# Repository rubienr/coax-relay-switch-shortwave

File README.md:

Shortwave Coax Switch for Antennas
__________________________________
* Very simple schema that switches up to four antenna relays.
* Needs poer just for switching process, remains without during radio operation.
* Up to 1.5KW with GUNNER 18V bistabile 25A AC relay.

Example
_______
The system contains of 4 PCBs:

* The input switch box:
  * 1x switch-matrix (ensures only one relay being active)
  * 1x relais-with-led-indicator (keeps the state, has LED indicator)

* The antenna switch box:
  * 1x switch-matrix (ensures only one relay being active)
  * 1x relais-with-led-indicator (keeps the state, LEDs optional)

Schema and PCB
______________
* Schemas
  * [switch-matrix](https://github.com/rubienr/coax-relay-switch-shortwave/blob/master/docs/switch-matrix-schema.pdf)
  * [relais-with-led-indicator](https://github.com/rubienr/coax-relay-switch-shortwave/blob/master/docs/led-indicator-schema.pdf)
* PCBs
  * [switch-matrix](https://github.com/rubienr/coax-relay-switch-shortwave/blob/master/docs/switch-matrix-pcb.pdf)
  * [relais-with-led-indicator](https://github.com/rubienr/coax-relay-switch-shortwave/blob/master/docs/relais-pcb.pdf)

Pictures
________

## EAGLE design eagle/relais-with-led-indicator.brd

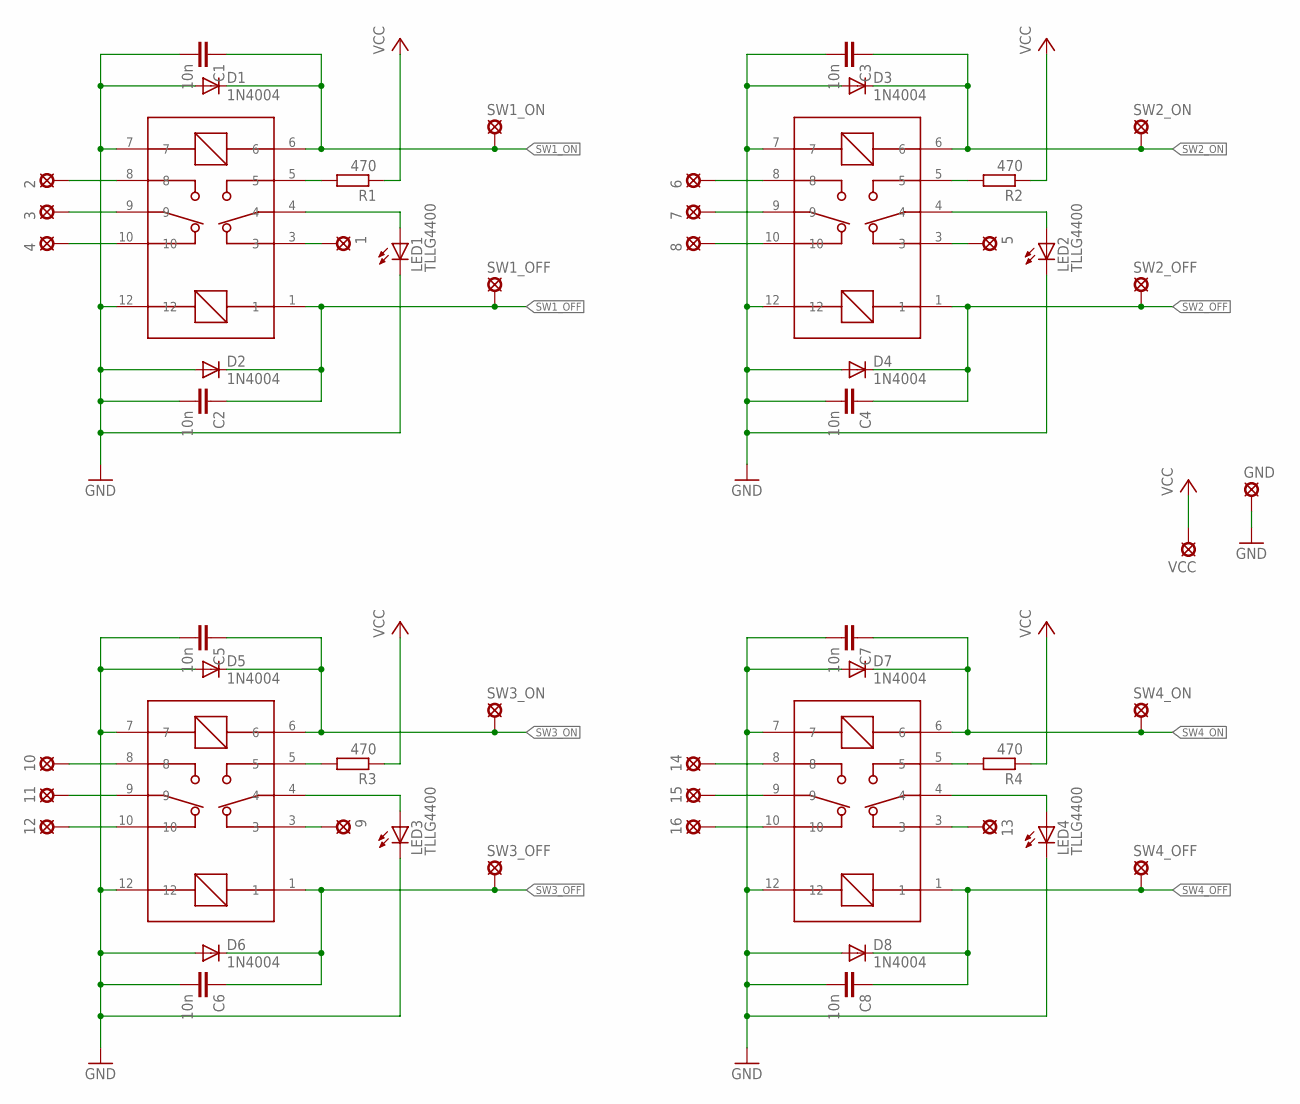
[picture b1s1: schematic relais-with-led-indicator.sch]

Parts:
1, 2, 3, 4, 5, 6, 7, 8, 9, 10, 11, 12, 13, 14, 15, 16: LSP10
C1, C2, C3, C4, C5, C6, C7, C8: 10n; C050-024X044
D1, D2, D3, D4, D5, D6, D7, D8: 1N4004; DO41-10
GND: LSP10
LED1, LED2, LED3, LED4: TLLG4400; LED3MM
R1, R2, R3, R4: 470; 0204/7
RL1, RL2, RL3, RL4: BISTABIL-2-COILS; BISTABILE-2-COILS
SW1_OFF, SW1_ON, SW2_OFF, SW2_ON, SW3_OFF, SW3_ON, SW4_OFF, SW4_ON: LSP10
VCC: LSP10

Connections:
GND: C1.2, C2.2, C3.2, C4.2, C5.2, C6.2, C7.2, C8.2, D1.A, D2.A, D3.A, D4.A, D5.A, D6.A, D7.A, D8.A, GND.MP, LED1.K (C), LED2.K (C), LED3.K (C), LED4.K (C), RL1.7, RL1.12, RL2.7, RL2.12, RL3.7, RL3.12, RL4.7, RL4.12
unnamed: LED1.A, RL1.4
unnamed: LED2.A, RL2.4
unnamed: 4.MP, RL1.10
unnamed: R2.2, RL2.5
unnamed: R1.2, RL1.5
unnamed: 8.MP, RL2.10
unnamed: 7.MP, RL2.9
unnamed: 6.MP, RL2.8
unnamed: 5.MP, RL2.3
unnamed: LED3.A, RL3.4
unnamed: 3.MP, RL1.9
unnamed: 2.MP, RL1.8
unnamed: 1.MP, RL1.3
unnamed: R3.2, RL3.5
unnamed: 12.MP, RL3.10
unnamed: 11.MP, RL3.9
unnamed: 10.MP, RL3.8
unnamed: 9.MP, RL3.3
unnamed: LED4.A, RL4.4
unnamed: R4.2, RL4.5
unnamed: 16.MP, RL4.10
unnamed: 15.MP, RL4.9
unnamed: 14.MP, RL4.8
unnamed: 13.MP, RL4.3
SW1_OFF: C2.1, D2.C, RL1.1, SW1_OFF.MP
SW1_ON: C1.1, D1.C, RL1.6, SW1_ON.MP
SW2_OFF: C4.1, D4.C, RL2.1, SW2_OFF.MP
SW2_ON: C3.1, D3.C, RL2.6, SW2_ON.MP
SW3_OFF: C6.1, D6.C, RL3.1, SW3_OFF.MP
SW3_ON: C5.1, D5.C, RL3.6, SW3_ON.MP
SW4_OFF: C8.1, D8.C, RL4.1, SW4_OFF.MP
SW4_ON: C7.1, D7.C, RL4.6, SW4_ON.MP
VCC: R1.1, R2.1, R3.1, R4.1, VCC.MP

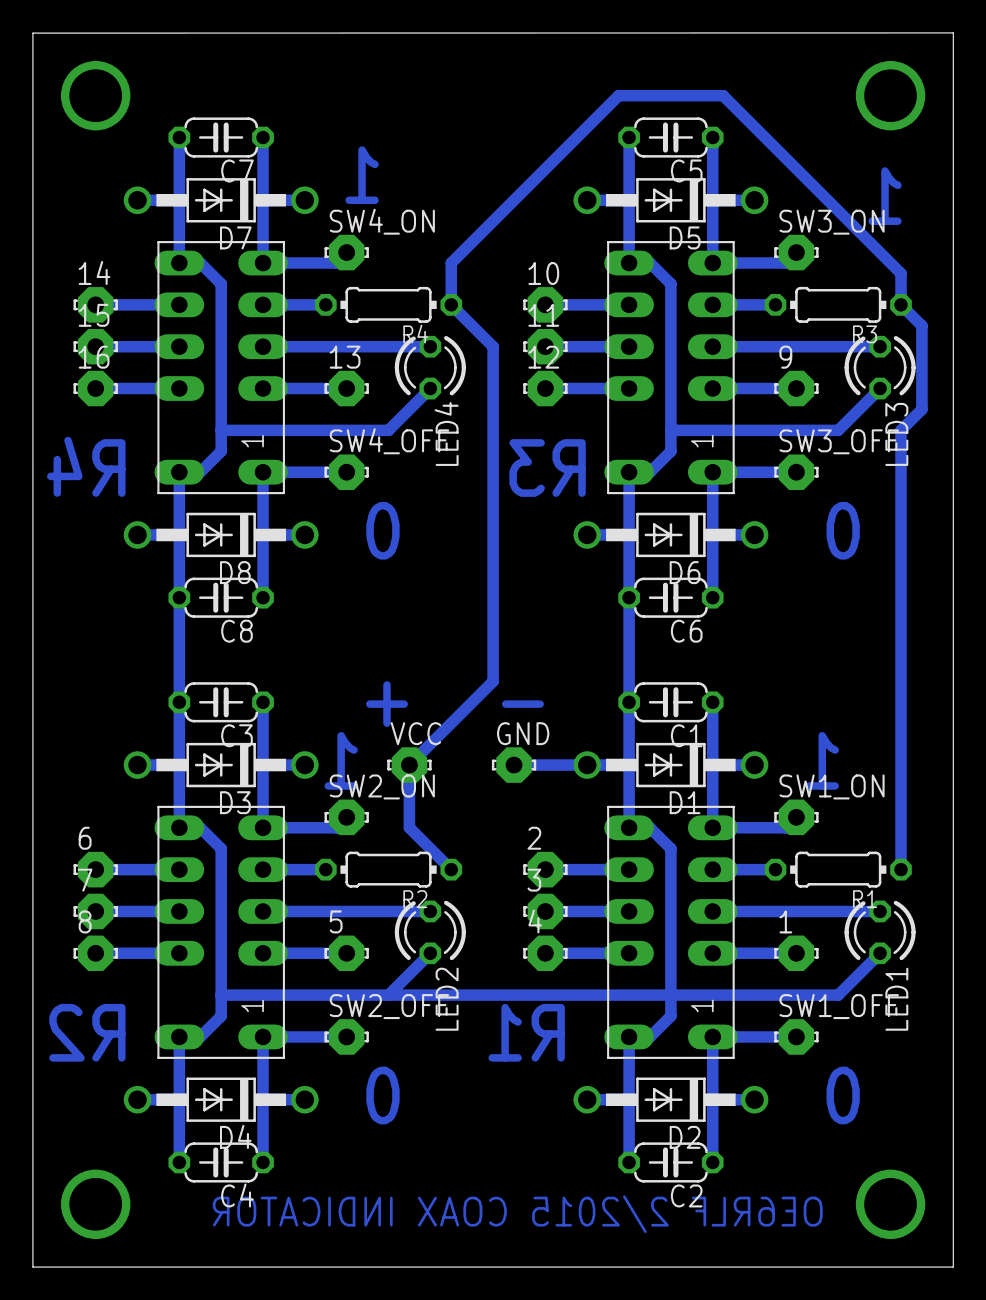
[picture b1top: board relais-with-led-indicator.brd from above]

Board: 2 copper layers, 55.9 x 74.9 mm, 54 parts (0 on the bottom side), 34 nets.

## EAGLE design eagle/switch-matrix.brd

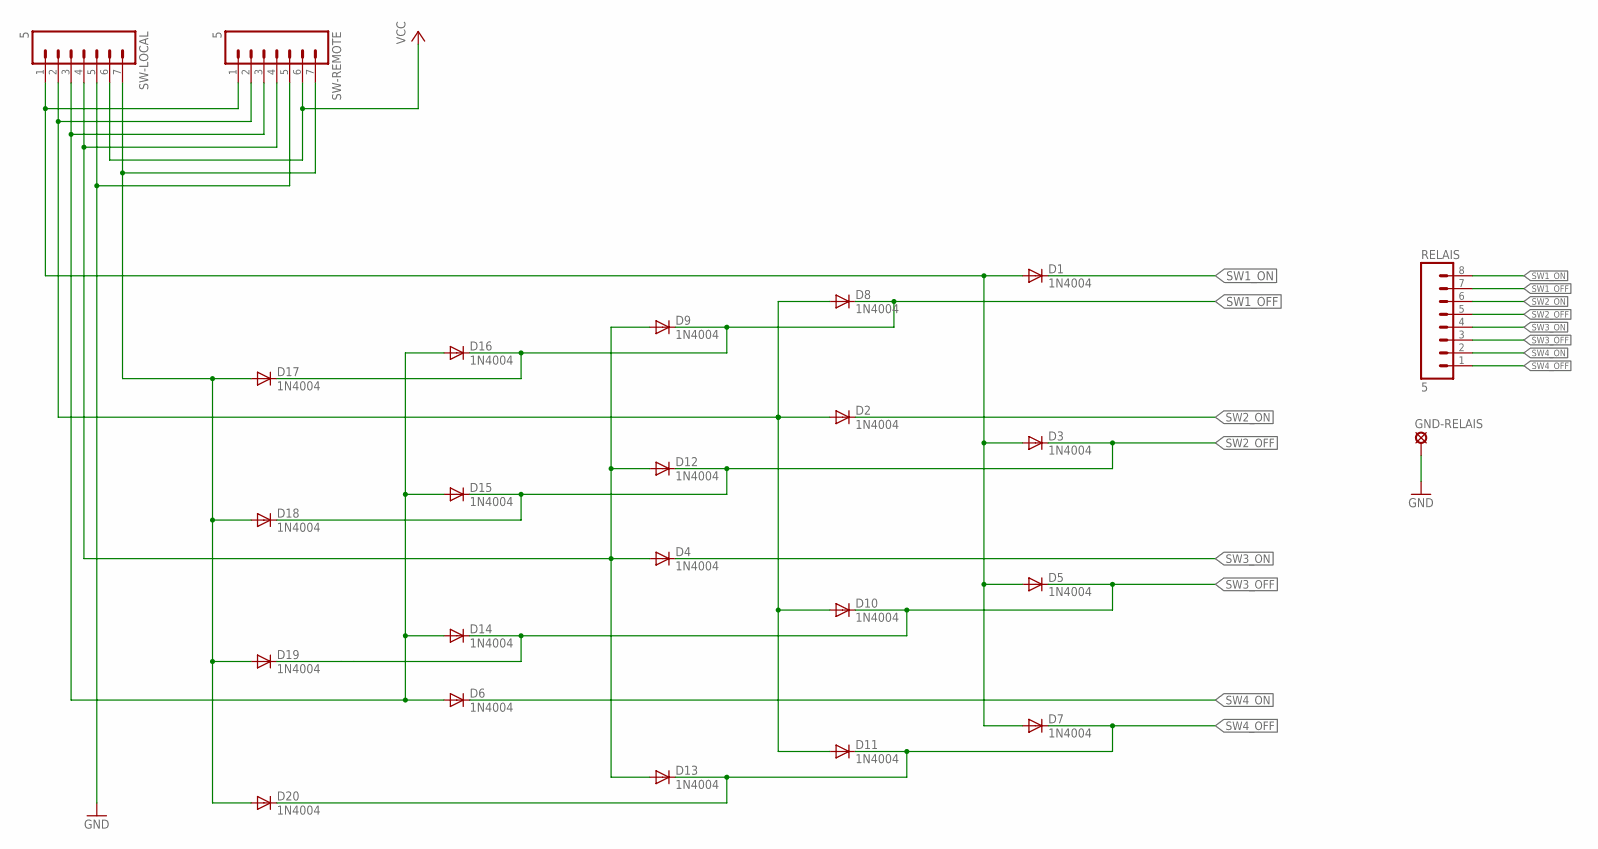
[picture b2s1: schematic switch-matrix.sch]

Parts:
D1, D2, D3, D4, D5, D6, D7, D8, D9, D10, D11, D12, D13, D14, D15, D16, D17, D18, D19, D20: 1N4004; DO41-10
GND-RELAIS: LSP10
RELAIS: 5; 08PA
SW-LOCAL: 5; 07PA
SW-REMOTE: 5; 07PA

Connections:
GND: GND-RELAIS.MP, SW-LOCAL.5, SW-REMOTE.5
unnamed: D1.A, D3.A, D5.A, D7.A, SW-LOCAL.1, SW-REMOTE.1
unnamed: D17.A, D18.A, D19.A, D20.A, SW-LOCAL.7, SW-REMOTE.7
unnamed: D4.A, D9.A, D12.A, D13.A, SW-LOCAL.4, SW-REMOTE.4
unnamed: D6.A, D14.A, D15.A, D16.A, SW-LOCAL.3, SW-REMOTE.3
unnamed: D2.A, D8.A, D10.A, D11.A, SW-LOCAL.2, SW-REMOTE.2
SW1_OFF: D8.C, D9.C, D16.C, D17.C, RELAIS.7
SW1_ON: D1.C, RELAIS.8
SW2_OFF: D3.C, D12.C, D15.C, D18.C, RELAIS.5
SW2_ON: D2.C, RELAIS.6
SW3_OFF: D5.C, D10.C, D14.C, D19.C, RELAIS.3
SW3_ON: D4.C, RELAIS.4
SW4_OFF: D7.C, D11.C, D13.C, D20.C, RELAIS.1
SW4_ON: D6.C, RELAIS.2
VCC: SW-LOCAL.6, SW-REMOTE.6

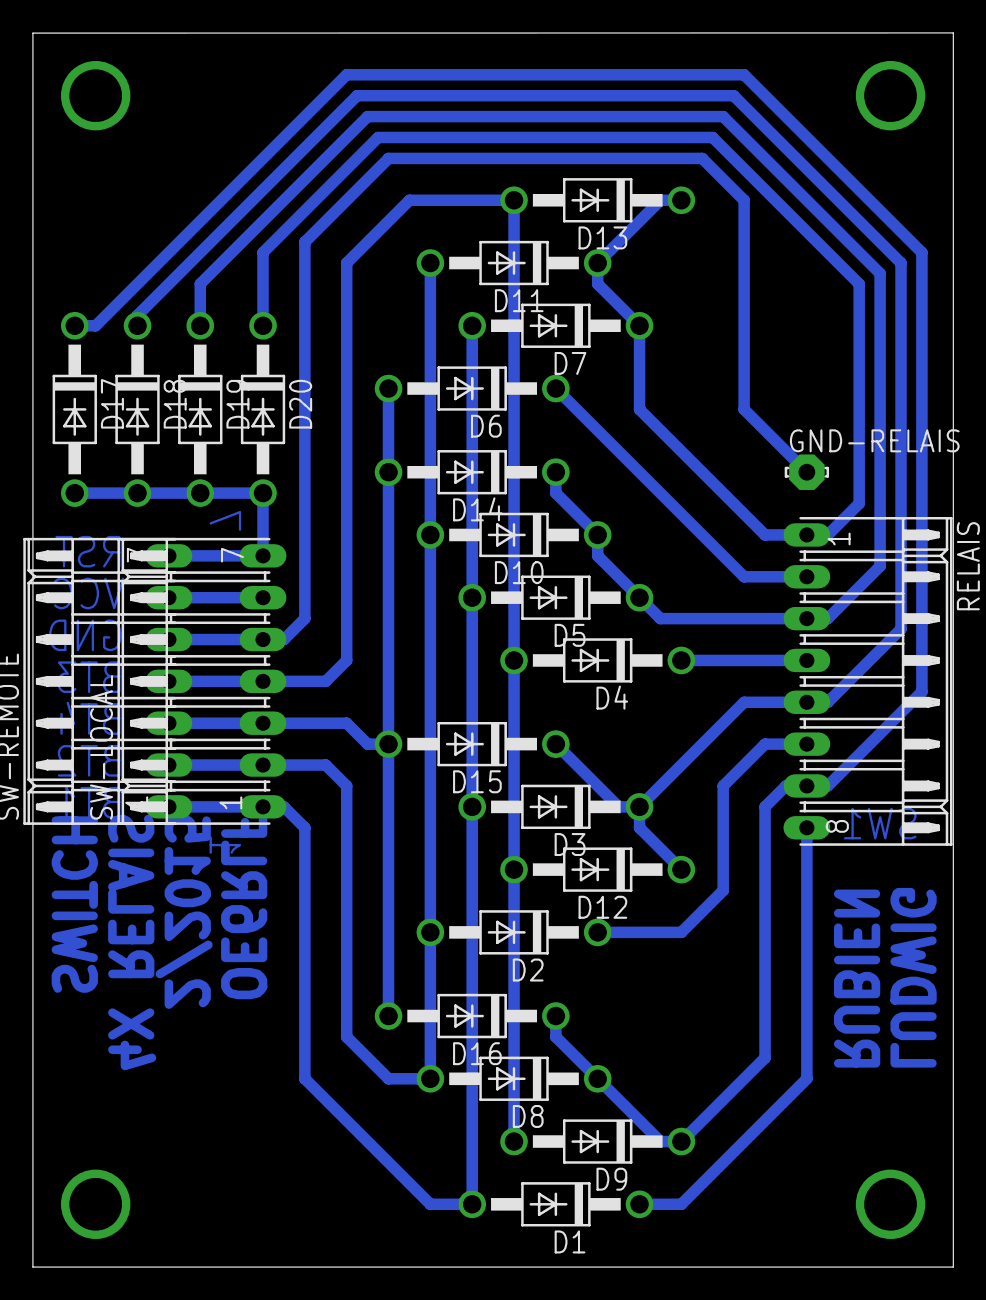
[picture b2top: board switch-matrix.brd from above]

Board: 2 copper layers, 55.9 x 74.9 mm, 24 parts (0 on the bottom side), 15 nets.

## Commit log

2016-01-24 more documentation...
2016-01-24 updated documentation
